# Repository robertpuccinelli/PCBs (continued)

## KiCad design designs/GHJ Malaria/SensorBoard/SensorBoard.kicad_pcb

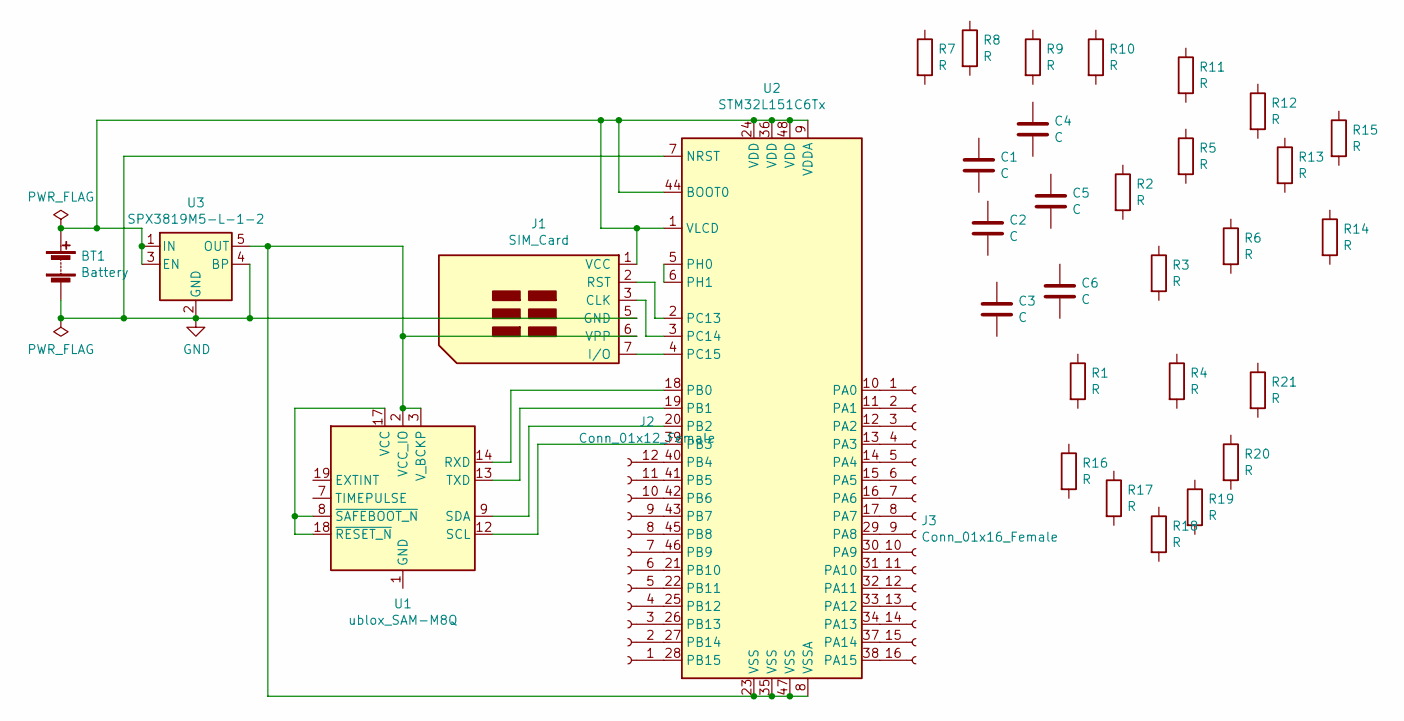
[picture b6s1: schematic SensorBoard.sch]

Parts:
BT1: Battery; BatteryHolder_Keystone_2468_2xAAA
C1, C2, C3, C4: C; C_1206_3216Metric
C5, C6: C; C_0603_1608Metric
J1: SIM_Card; USB_Mini-B_Lumberg_2486_01_Horizontal
J2: Conn_01x12_Female; PinSocket_1x12_P2.54mm_Vertical_SMD_Pin1Right
J3: Conn_01x16_Female; PinSocket_1x16_P2.54mm_Vertical_SMD_Pin1Right
R1, R2, R3, R7, R8, R9: R; R_01005_0402Metric
R4, R5, R6: R; R_0815_2038Metric
R10, R11, R12, R13, R14, R15, R16, R17, R18, R19, R20, R21: R; R_0603_1608Metric
U1: ublox_SAM-M8Q; SSOP-20_4.4x6.5mm_P0.65mm
U2: STM32L151C6Tx; LQFP-48_7x7mm_P0.5mm
U3: SPX3819M5-L-1-2; SOT-23-5

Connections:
GND: BT1.2 (-), J1.5 (GND), U2.7 (NRST), U3.2 (GND), U3.4 (BP)
unnamed: BT1.1 (+), J1.1 (VCC), U2.1 (VLCD), U2.9 (VDDA), U2.24 (VDD), U2.36 (VDD), U2.44 (BOOT0), U2.48 (VDD), U3.1 (IN), U3.3 (EN)
unnamed: J1.2 (RST), U2.2 (PC13)
unnamed: J1.3 (CLK), U2.3 (PC14)
unnamed: J1.6 (VPP), U1.2 (VCC_IO), U1.3 (V_BCKP), U2.8 (VSSA), U2.23 (VSS), U2.35 (VSS), U2.47 (VSS), U3.5 (OUT)
unnamed: J1.7 (I/O), U2.4 (PC15)
unnamed: J2.1, U2.28 (PB15)
unnamed: J2.2, U2.27 (PB14)
unnamed: J2.3, U2.26 (PB13)
unnamed: J2.4, U2.25 (PB12)
unnamed: J2.5, U2.22 (PB11)
unnamed: J2.6, U2.21 (PB10)
unnamed: J2.7, U2.46 (PB9)
unnamed: J2.8, U2.45 (PB8)
unnamed: J2.9, U2.43 (PB7)
unnamed: J2.10, U2.42 (PB6)
unnamed: J2.11, U2.41 (PB5)
unnamed: J2.12, U2.40 (PB4)
unnamed: J3.1, U2.10 (PA0)
unnamed: J3.2, U2.11 (PA1)
unnamed: J3.3, U2.12 (PA2)
unnamed: J3.4, U2.13 (PA3)
unnamed: J3.5, U2.14 (PA4)
unnamed: J3.6, U2.15 (PA5)
unnamed: J3.7, U2.16 (PA6)
unnamed: J3.8, U2.17 (PA7)
unnamed: J3.9, U2.29 (PA8)
unnamed: J3.10, U2.30 (PA9)
unnamed: J3.11, U2.31 (PA10)
unnamed: J3.12, U2.32 (PA11)
unnamed: J3.13, U2.33 (PA12)
unnamed: J3.14, U2.34 (PA13)
unnamed: J3.15, U2.37 (PA14)
unnamed: J3.16, U2.38 (PA15)
unnamed: U1.1 (GND), U1.4 (GND), U1.5 (GND), U1.6 (GND), U1.10 (GND), U1.11 (GND), U1.15 (GND), U1.16 (GND), U1.20 (GND)
unnamed: U1.9 (SDA), U2.20 (PB2)
unnamed: U1.12 (SCL), U2.39 (PB3)
unnamed: U1.13 (TXD), U2.19 (PB1)
unnamed: U1.14 (RXD), U2.18 (PB0)
unnamed: U1.8 (~SAFEBOOT_N), U1.17 (VCC), U1.18 (~RESET_N)
unnamed: U2.5 (PH0), U2.6 (PH1)

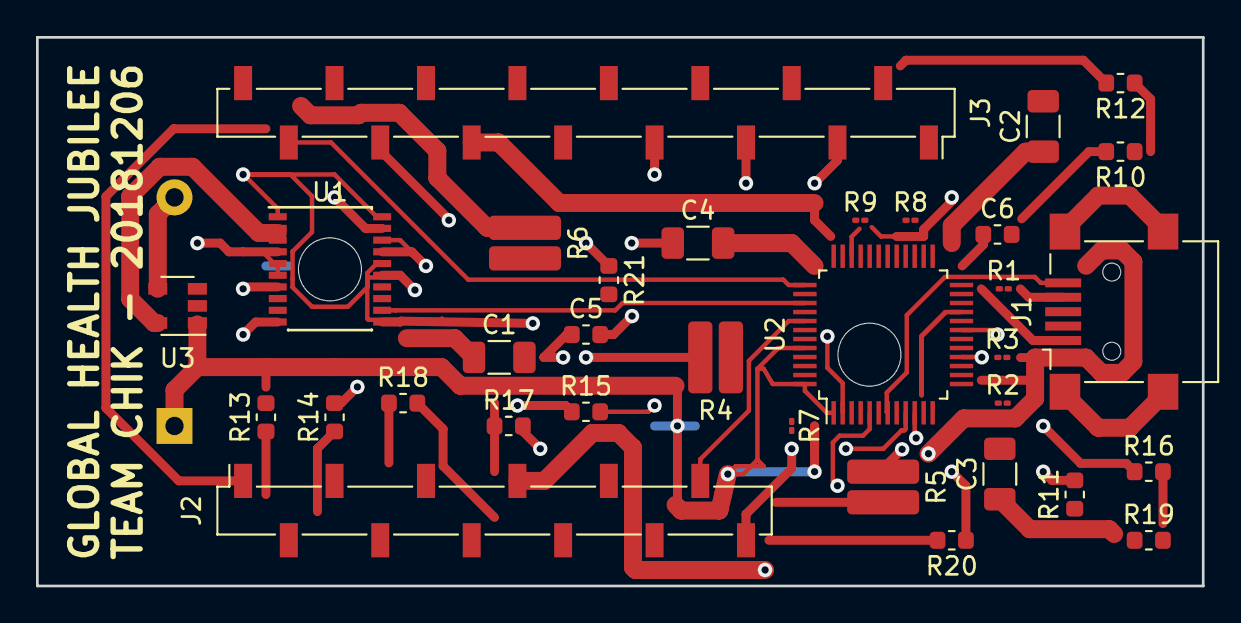
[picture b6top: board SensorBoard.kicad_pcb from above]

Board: 2 copper layers, 64.8 x 30.5 mm, 34 parts (1 on the bottom side), 40 nets.

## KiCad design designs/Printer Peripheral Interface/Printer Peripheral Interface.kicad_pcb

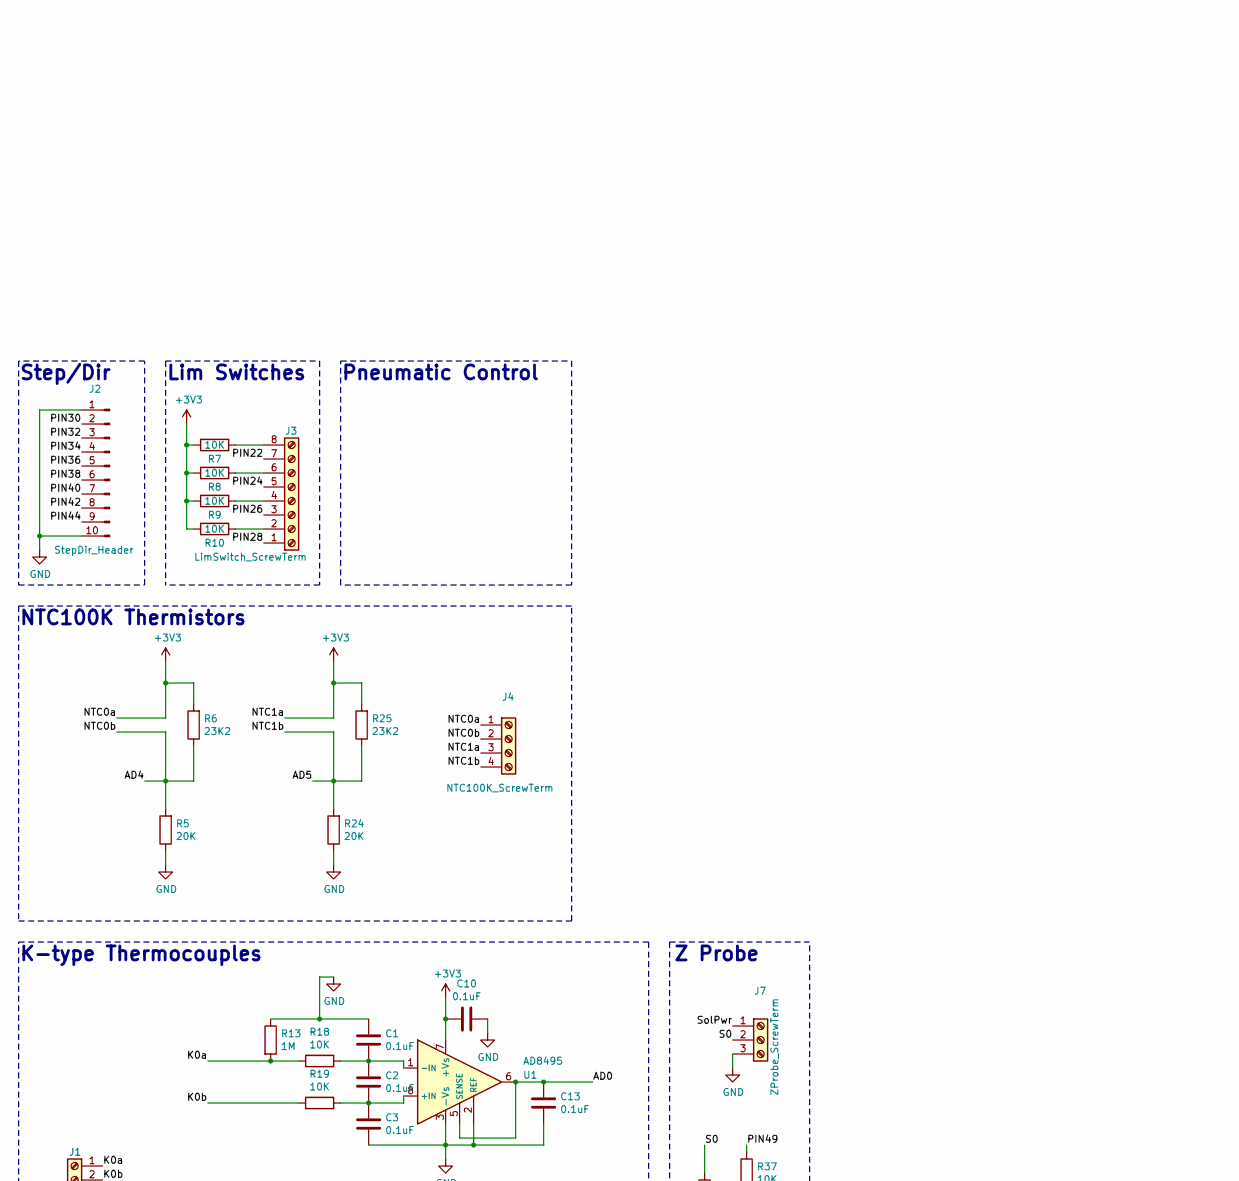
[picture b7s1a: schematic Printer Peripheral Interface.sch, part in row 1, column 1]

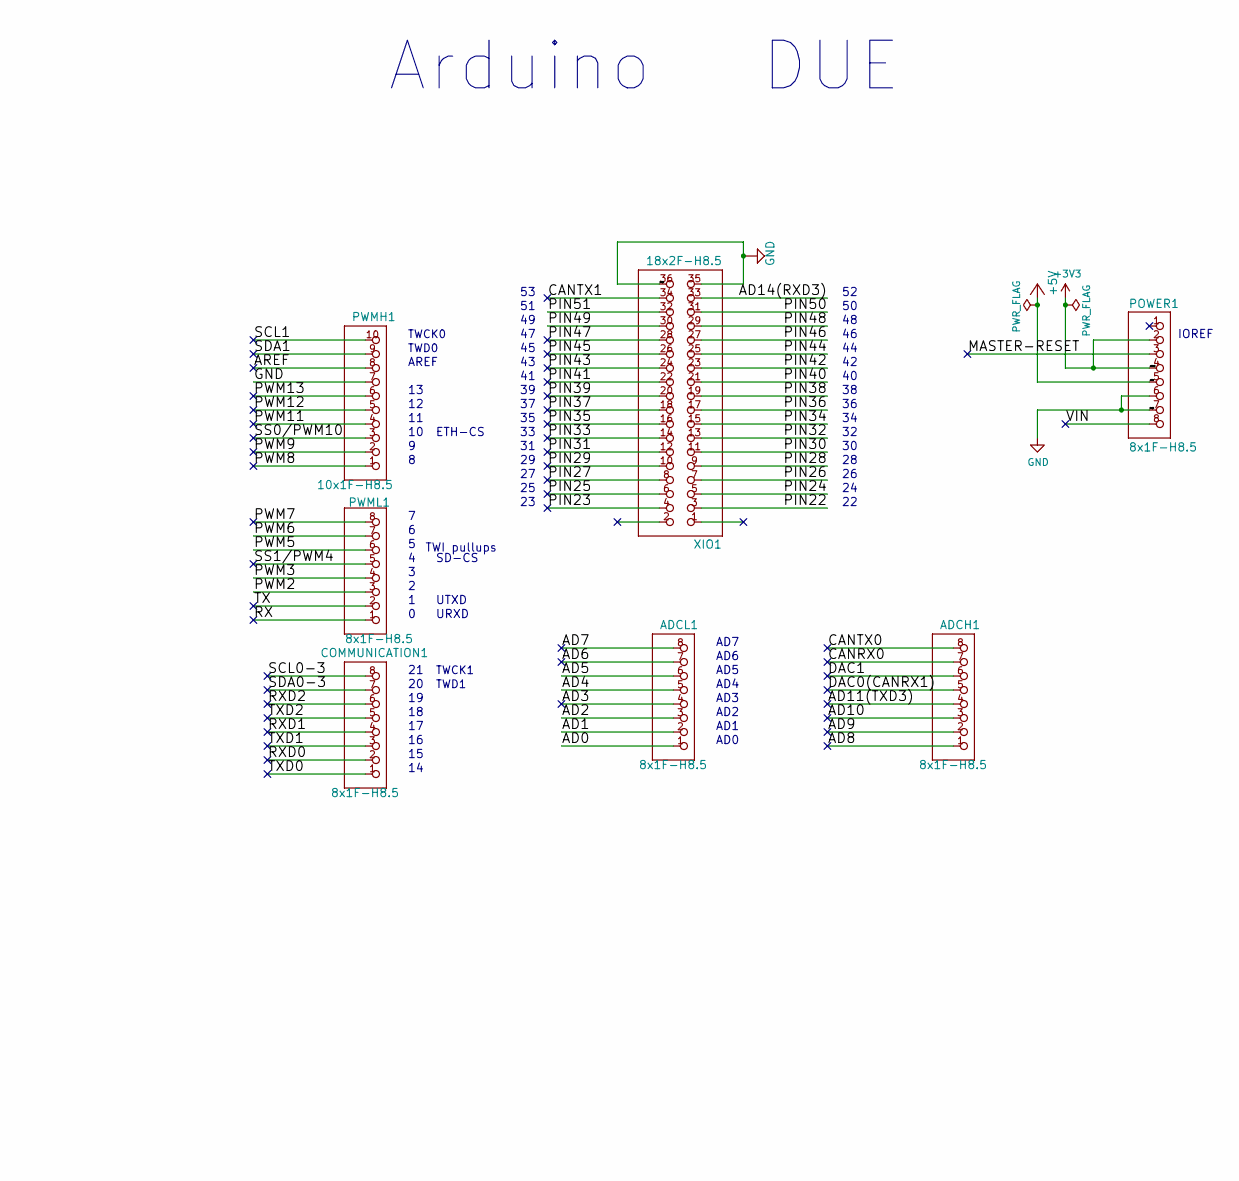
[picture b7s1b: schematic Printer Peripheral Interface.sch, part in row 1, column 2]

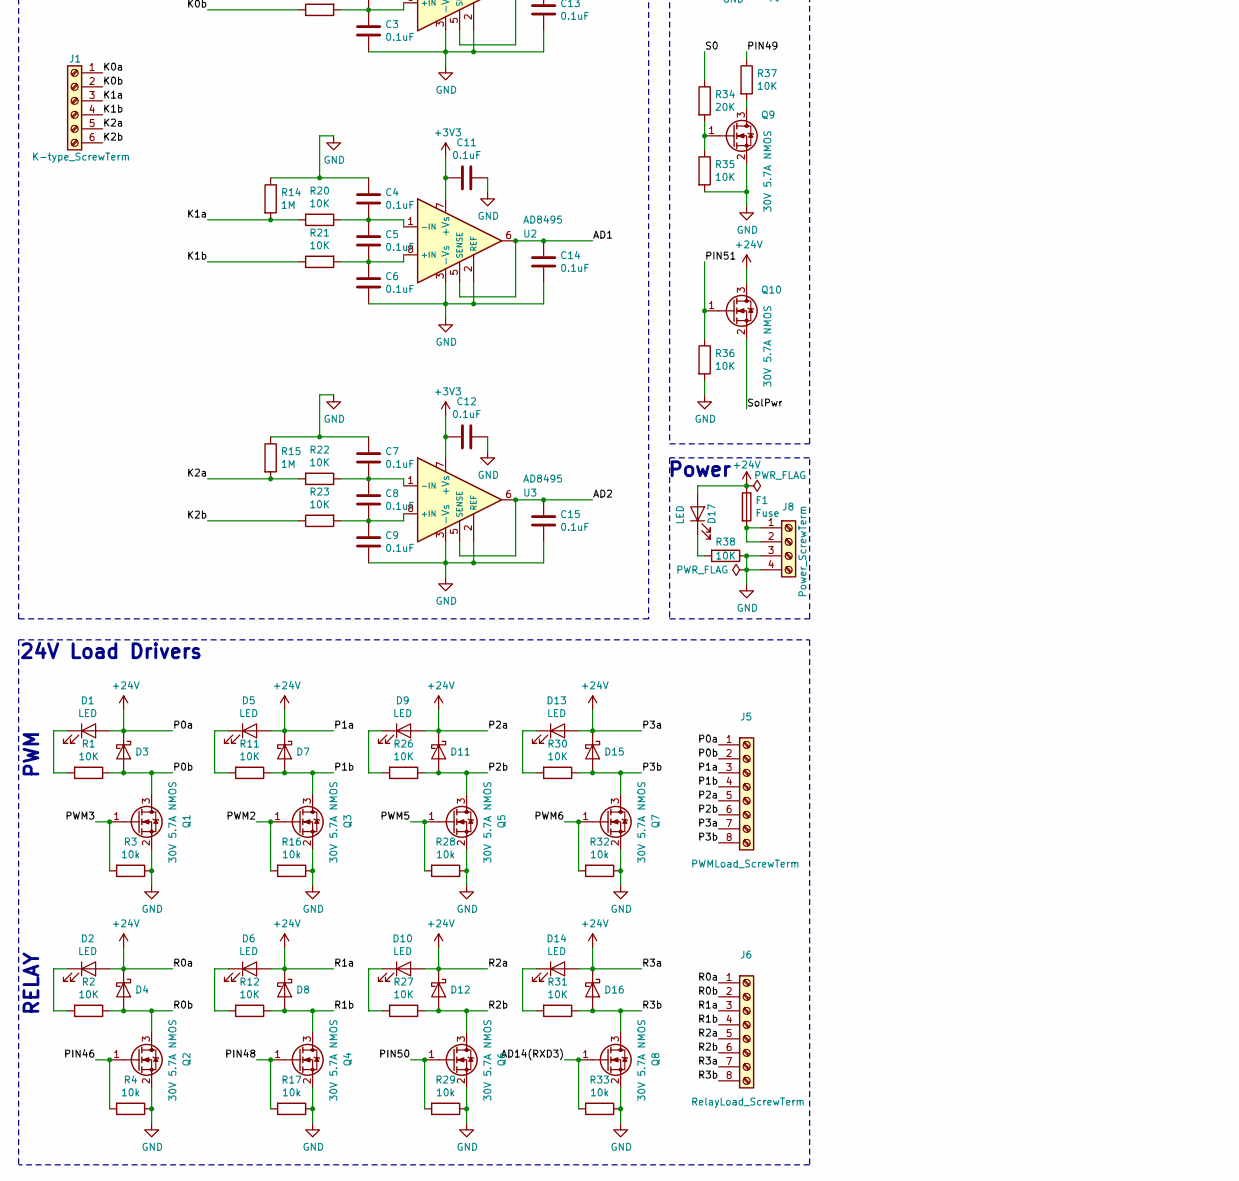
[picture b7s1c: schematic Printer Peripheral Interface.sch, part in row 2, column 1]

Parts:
ADCH1: 8x1F-H8.5; 1X08
ADCL1: 8x1F-H8.5; 1X08
C1, C2, C3, C4, C5, C6, C7, C8, C9, C10, C11, C12, C13, C14, C15: 0.1uF; C_0603_1608Metric
COMMUNICATION1: 8x1F-H8.5; 1X08
D1, D2, D5, D6, D9, D10, D13, D14, D17: LED; LED_0603_1608Metric
D3, D4, D7, D8, D11, D12, D15, D16: D_Schottky; D_SOD-123
F1: Fuse; Littelfuse_154Holder_Custom
J1: K-type_ScrewTerm; TerminalBlock_Phoenix_PT-1,5-6-3.5-H_1x06_P3.50mm_Horizontal
J2: StepDir_Header; PinHeader_1x10_P2.54mm_Vertical
J3: LimSwitch_ScrewTerm; TerminalBlock_Phoenix_PT-1,5-8-3.5-H_1x08_P3.50mm_Horizontal
J4: NTC100K_ScrewTerm; TerminalBlock_Phoenix_PT-1,5-4-3.5-H_1x04_P3.50mm_Horizontal
J5: PWMLoad_ScrewTerm; TerminalBlock_Phoenix_PT-1,5-8-3.5-H_1x08_P3.50mm_Horizontal
J6: RelayLoad_ScrewTerm; TerminalBlock_Phoenix_PT-1,5-8-3.5-H_1x08_P3.50mm_Horizontal
J7: ZProbe_ScrewTerm; TerminalBlock_Phoenix_PT-1,5-3-3.5-H_1x03_P3.50mm_Horizontal
J8: Power_ScrewTerm; TerminalBlock_Phoenix_PT-1,5-4-3.5-H_1x04_P3.50mm_Horizontal
POWER1: 8x1F-H8.5; 1X08
PWMH1: 10x1F-H8.5; 1X10
PWML1: 8x1F-H8.5; 1X08
Q1, Q2, Q3, Q4, Q5, Q6, Q7, Q8, Q9, Q10: 30V 5.7A NMOS; SOT-23
R1, R2, R7, R8, R9, R10, R11, R12, R18, R19, R20, R21, R22, R23, R26, R27, R30, R31, R35, R36, R37, R38: 10K; R_0603_1608Metric
R3, R4, R16, R17, R28, R29, R32, R33: 10k; R_0603_1608Metric
R5, R24, R34: 20K; R_0603_1608Metric
R6, R25: 23K2; R_0603_1608Metric
R13, R14, R15: 1M; R_0603_1608Metric
U1, U2, U3: AD8495; MSOP-8_3x3mm_P0.65mm
XIO1: 18x2F-H8.5; 2X18

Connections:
+3V3: C10.2, C11.2, C12.2, J4.1, J4.3, POWER1.2, POWER1.4, R6.2, R7.2, R8.2, R9.2, R10.2, R25.2, U1.7 (+Vs), U2.7 (+Vs), U3.7 (+Vs)
+5V: POWER1.5
+24V: D1.2 (A), D2.2 (A), D3.1 (K), D4.1 (K), D5.2 (A), D6.2 (A), D7.1 (K), D8.1 (K), D9.2 (A), D10.2 (A), D11.1 (K), D12.1 (K), D13.2 (A), D14.2 (A), D15.1 (K), D16.1 (K), D17.2 (A), F1.1, J5.1, J5.3, J5.5, J5.7, J6.1, J6.3, J6.5, J6.7, Q10.3 (D)
/AD0: ADCL1.1, C13.1, U1.5 (SENSE), U1.6
/AD1: ADCL1.2, C14.1, U2.5 (SENSE), U2.6
/AD2: ADCL1.3, C15.1, U3.5 (SENSE), U3.6
/AD3: ADCL1.4
/AD4: ADCL1.5, J4.2, R5.2, R6.1
/AD5: ADCL1.6, J4.4, R24.2, R25.1
/AD6: ADCL1.7
/AD7: ADCL1.8
/AD8: ADCH1.1
/AD9: ADCH1.2
/AD10: ADCH1.3
/AD11(TXD3): ADCH1.4
/AD14(RXD3): Q8.1 (G), R33.2, XIO1.33
/AREF: PWMH1.8
/CANRX0: ADCH1.7
/CANTX0: ADCH1.8
/CANTX1: XIO1.34
/DAC0(CANRX1): ADCH1.5
/DAC1: ADCH1.6
/K0a: J1.1, R13.2, R18.2
/K0b: J1.2, R19.1
/K1a: J1.3, R14.2, R20.2
/K1b: J1.4, R21.1
/K2a: J1.5, R15.2, R22.2
/K2b: J1.6, R23.1
/MASTER-RESET: POWER1.3
/P0b: D3.2 (A), J5.2, Q1.3 (D), R1.1
/P1b: D7.2 (A), J5.4, Q3.3 (D), R11.1
/P2b: D11.2 (A), J5.6, Q5.3 (D), R26.1
/P3b: D15.2 (A), J5.8, Q7.3 (D), R30.1
/PIN22: J3.7, XIO1.3
/PIN23: XIO1.4
/PIN24: J3.5, XIO1.5
/PIN25: XIO1.6
/PIN26: J3.3, XIO1.7
/PIN27: XIO1.8
/PIN28: J3.1, XIO1.9
/PIN29: XIO1.10
/PIN30: J2.2, XIO1.11
/PIN31: XIO1.12
/PIN32: J2.3, XIO1.13
/PIN33: XIO1.14
/PIN34: J2.4, XIO1.15
/PIN35: XIO1.16
/PIN36: J2.5, XIO1.17
/PIN37: XIO1.18
/PIN38: J2.6, XIO1.19
/PIN39: XIO1.20
/PIN40: J2.7, XIO1.21
/PIN41: XIO1.22
/PIN42: J2.8, XIO1.23
/PIN43: XIO1.24
/PIN44: J2.9, XIO1.25
/PIN45: XIO1.26
/PIN46: Q2.1 (G), R4.2, XIO1.27
/PIN47: XIO1.28
/PIN48: Q4.1 (G), R17.2, XIO1.29
/PIN49: R37.1, XIO1.30
/PIN50: Q6.1 (G), R29.2, XIO1.31
/PIN51: Q10.1 (G), R36.1, XIO1.32
/PWM2: PWML1.3, Q3.1 (G), R16.2
/PWM3: PWML1.4, Q1.1 (G), R3.2
/PWM5: PWML1.6, Q5.1 (G), R28.2
/PWM6: PWML1.7, Q7.1 (G), R32.2
/PWM7: PWML1.8
/PWM8: PWMH1.1
/PWM9: PWMH1.2
/PWM11: PWMH1.4
/PWM12: PWMH1.5
/PWM13: PWMH1.6
/R0b: D4.2 (A), J6.2, Q2.3 (D), R2.1
/R1b: D8.2 (A), J6.4, Q4.3 (D), R12.1
/R2b: D12.2 (A), J6.6, Q6.3 (D), R27.1
/R3b: D16.2 (A), J6.8, Q8.3 (D), R31.1
/RX: PWML1.1
/RXD0: COMMUNICATION1.2
/RXD1: COMMUNICATION1.4
/RXD2: COMMUNICATION1.6
/S0: J7.2, R34.1
/SCL0-3: COMMUNICATION1.8
/SCL1: PWMH1.10
/SDA0-3: COMMUNICATION1.7
/SDA1: PWMH1.9
/SS0/PWM10: PWMH1.3
/SS1/PWM4: PWML1.5
/SolPwr: J7.1, Q10.2 (S)
/TX: PWML1.2
/TXD0: COMMUNICATION1.1
/TXD1: COMMUNICATION1.3
/TXD2: COMMUNICATION1.5
/VIN: POWER1.8
GND: C1.1, C3.2, C4.1, C6.2, C7.1, C9.2, C10.1, C11.1, C12.1, C13.2, C14.2, C15.2, J2.1, J2.10, J7.3, J8.3, J8.4, POWER1.6, POWER1.7, PWMH1.7, Q1.2 (S), Q2.2 (S), Q3.2 (S), Q4.2 (S), Q5.2 (S), Q6.2 (S), Q7.2 (S), Q8.2 (S), Q9.2 (S), R3.1, R4.1, R5.1, R13.1, R14.1, R15.1, R16.1, R17.1, R24.1, R28.1, R29.1, R32.1, R33.1, R35.2, R36.2, R38.1, U1.2 (REF), U1.3 (-Vs), U2.2 (REF), U2.3 (-Vs), U3.2 (REF), U3.3 (-Vs), XIO1.35, XIO1.36
unnamed: C1.2, C2.1, R18.1, U1.1 (-IN)
unnamed: C2.2, C3.1, R19.2, U1.8 (+IN)
unnamed: C4.2, C5.1, R20.1, U2.1 (-IN)
unnamed: C5.2, C6.1, R21.2, U2.8 (+IN)
unnamed: C7.2, C8.1, R22.1, U3.1 (-IN)
unnamed: C8.2, C9.1, R23.2, U3.8 (+IN)
unnamed: D1.1 (K), R1.2
unnamed: D2.1 (K), R2.2
unnamed: D5.1 (K), R11.2
unnamed: D6.1 (K), R12.2
unnamed: D9.1 (K), R26.2
unnamed: D10.1 (K), R27.2
unnamed: D13.1 (K), R30.2
unnamed: D14.1 (K), R31.2
unnamed: D17.1 (K), R38.2
unnamed: F1.2, J8.1, J8.2
unnamed: J3.2, R10.1
unnamed: J3.4, R9.1
unnamed: J3.6, R8.1
unnamed: J3.8, R7.1
unnamed: Q9.1 (G), R34.2, R35.1
unnamed: Q9.3 (D), R37.2

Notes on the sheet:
TWI pullups
TWCK1
TWD1
IOREF
TWCK0
TWD0
AD1
AD2
AD3
AD4
AD5
AD6
AD0
AREF
AD7
SD-CS
UTXD
URXD
ETH-CS
Arduino DUE
K-type Thermocouples
NTC100K Thermistors
24V Load Drivers
Step/Dir
Lim Switches
PWM
RELAY
Pneumatic Control
Power
Z Probe

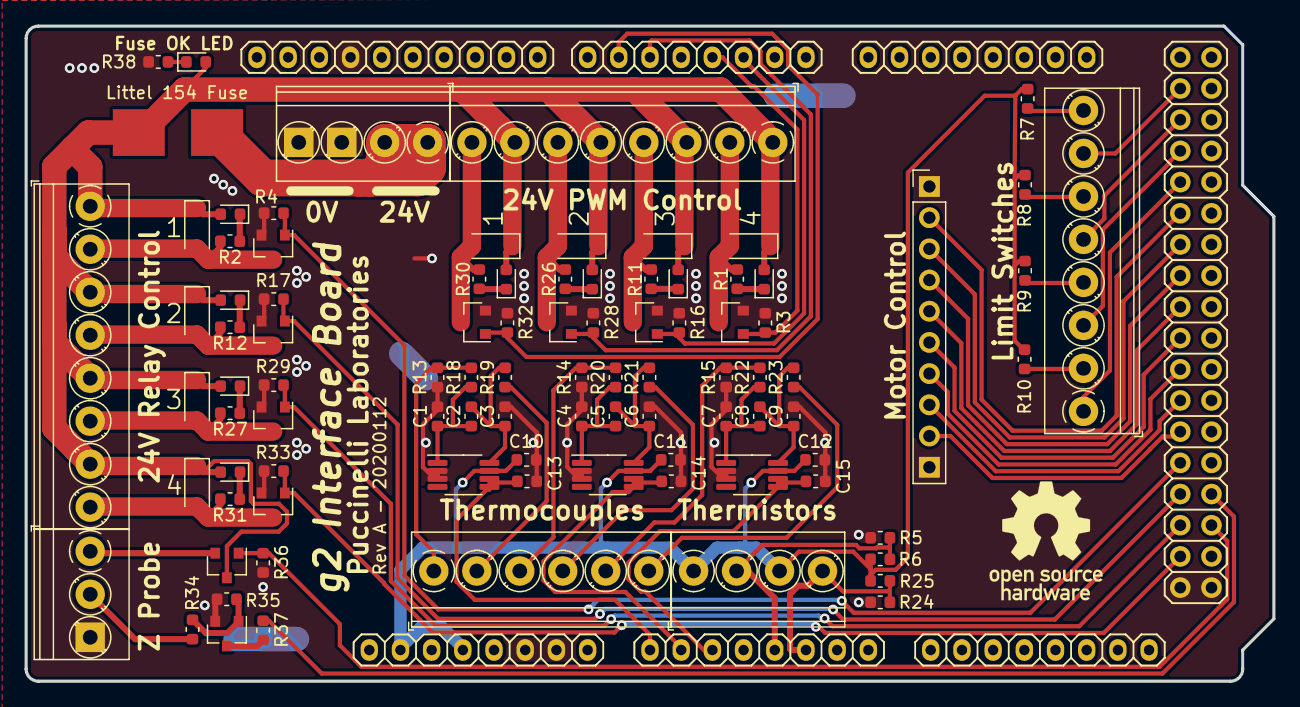
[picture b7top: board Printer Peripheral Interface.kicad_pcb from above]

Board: 2 copper layers, 101.6 x 53.3 mm, 99 parts (0 on the bottom side), 68 nets.

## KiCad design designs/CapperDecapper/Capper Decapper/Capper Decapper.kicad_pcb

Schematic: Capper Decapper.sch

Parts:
C1, C3, C7, C9, C13, C15, C22, C24: 22nF; C_0603_1608Metric
C2, C6, C8, C12, C14, C19, C23, C28, C29, C34, C35, C36, C37: 0.1uF; C_0603_1608Metric
C4, C10, C16, C25: 2.2uF; C_0603_1608Metric
C5, C11, C18, C27: 10nF; C_0603_1608Metric
C17, C20, C30, C31, C32, C33: 10uF; CP_EIA-3528-12_Kemet-T
C21: 0.33uF; C_0603_1608Metric
C26: 0.01uF; C_0603_1608Metric
D1, D2: Schottky; D_SMA
J1: Pi Control Signals; PinSocket_1x24_P2.54mm_Vertical
J2: Motor_Power; PinSocket_1x20_P2.54mm_Vertical
J3: Screw_Term; TerminalBlock_4Ucon_1x02_P3.50mm_Horizontal
L1: 22uH; L_Wuerth_HCI-1365
MH1, MH2: MountingHole; MountingHole_3mm
R1, R6, R7, R10, R12, R15, R16, R19: 0.05R; R_1206_3216Metric
R2, R5, R8, R9, R13, R14, R17, R18: 20k; R_0603_1608Metric
R3, R4: 330R; R_0603_1608Metric
R20: 14.2K; R_0603_1608Metric
R21: 2K; R_0603_1608Metric
U1, U4, U5, U8, U9, U12, U13, U18: INA214; SOT-363_SC-70-6
U2, U6, U10, U15: 74AHC08; PVQFN-14
U3, U7, U11, U16: DRV8833RTY; WQFN-16-1EP_4x4mm_P0.65mm_EP2.1x2.1mm
U14: L7805; TO-252-3_TabPin2
U17: MAX6018BEUR16; SOT-23
U19: AP1501A; TO-263-5_TabPin3

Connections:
/3.3V: J1.23, U17.1
/5V: C2.1, C6.1, C8.1, C12.1, C14.1, C19.1, C23.1, C28.1, C29.2, C34.1, C35.1, C36.1, C37.1, J1.22, U1.3 (V+), U2.14, U3.15, U4.3 (V+), U5.3 (V+), U6.14, U7.15, U8.3 (V+), U9.3 (V+), U10.14, U11.15, U12.3 (V+), U13.3 (V+), U14.3 (OUT), U15.14, U16.15, U18.3 (V+)
/ADC1: C3.1, J1.14, R5.1
/ADC2: C1.2, J1.15, R2.2
/ADC3: C9.1, J1.16, R9.1
/ADC4: C7.2, J1.17, R8.2
/ADC5: C15.1, J1.18, R14.1
/ADC6: C13.2, J1.19, R13.2
/ADC7: C24.1, J1.20, R18.1
/ADC8: C22.2, J1.21, R17.2
/EN1: J1.4, U2.10, U2.13
/EN2: J1.5, U2.2, U2.5
/EN3: J1.6, U6.10, U6.13
/EN4: J1.7, U6.2, U6.5
/EN5: J1.8, U10.10, U10.13
/EN6: J1.9, U10.2, U10.5
/EN7: J1.10, U15.10, U15.13
/EN8: J1.11, U15.2, U15.5
/FWD: J1.13, U2.1, U2.9, U6.1, U6.9, U10.1, U10.9, U15.1, U15.9
/MOT1_1: J2.4, R6.1, U4.4 (IN+)
/MOT1_2: J2.5, U3.2
/MOT2_1: J2.6, R1.2, U1.5 (IN-)
/MOT2_2: J2.7, U3.3
/MOT3_1: J2.8, R10.1, U8.4 (IN+)
/MOT3_2: J2.9, U7.2
/MOT4_1: J2.10, R7.2, U5.5 (IN-)
/MOT4_2: J2.11, U7.3
/MOT5_1: J2.12, R15.1, U12.4 (IN+)
/MOT5_2: J2.13, U11.2
/MOT6_1: J2.14, R12.2, U9.5 (IN-)
/MOT6_2: J2.15, U11.3
/MOT7_1: J2.16, R19.1, U18.4 (IN+)
/MOT7_2: J2.17, U16.2
/MOT8_1: J2.18, R16.2, U13.5 (IN-)
/MOT8_2: J2.19, U16.3
/REV: J1.12, U2.4, U2.12, U6.4, U6.12, U10.4, U10.12, U15.4, U15.12
/SOLSET: J1.3; also elsewhere on the board
/SW1: J2.2, R4.1
/SW2: J2.3, R3.2
/V_mon: C26.1, U1.1 (REF), U4.1 (REF), U5.1 (REF), U8.1 (REF), U9.1 (REF), U12.1 (REF), U13.1 (REF), U17.2, U18.1 (REF)
/V_motor: C5.2, C11.2, C17.1, C18.2, C20.1, C27.2, C30.1, C32.1, C33.1, L1.2, R20.2, U3.10, U7.10, U11.10, U16.10
GND: C1.1, C2.2, C3.2, C4.1, C6.2, C7.1, C8.2, C9.2, C10.1, C12.2, C13.1, C14.2, C15.2, C16.1, C17.2, C19.2, C20.2, C21.1, C22.1, C23.2, C24.2, C25.1, C26.2, C28.2, C29.1, C30.2, C31.2, C32.2, C33.2, C34.2, C35.2, C36.2, C37.2, D1.2, D2.2, J1.24, J2.20, J3.1, R21.2, U1.2 (GND), U2.7, U2.15, U3.1, U3.4, U3.11, U3.17, U4.2 (GND), U5.2 (GND), U6.7, U6.15, U7.1, U7.4, U7.11, U7.17, U8.2 (GND), U9.2 (GND), U10.7, U10.15, U11.1, U11.4, U11.11, U11.17, U12.2 (GND), U13.2 (GND), U14.2 (GND), U15.7, U15.15, U16.1, U16.4, U16.11, U16.17, U17.3, U18.2 (GND), U19.3, U19.5; also elsewhere on the board
unnamed: C4.2, U3.12
unnamed: C5.1, U3.9
unnamed: C10.2, U7.12
unnamed: C11.1, U7.9
unnamed: C16.2, U11.12
unnamed: C18.1, U11.9
unnamed: C25.2, U16.12
unnamed: C27.1, U16.9
unnamed: D2.1, L1.1, U19.2
unnamed: J1.1, R3.1
unnamed: J1.2, R4.2
unnamed: R1.1, U1.4 (IN+), U3.5
unnamed: R2.1, U1.6 (OUT)
unnamed: R5.2, U4.6 (OUT)
unnamed: R6.2, U3.16, U4.5 (IN-)
unnamed: R7.1, U5.4 (IN+), U7.5
unnamed: R8.1, U5.6 (OUT)
unnamed: R9.2, U8.6 (OUT)
unnamed: R10.2, U7.16, U8.5 (IN-)
unnamed: R12.1, U9.4 (IN+), U11.5
unnamed: R13.1, U9.6 (OUT)
unnamed: R14.2, U12.6 (OUT)
unnamed: R15.2, U11.16, U12.5 (IN-)
unnamed: R16.1, U13.4 (IN+), U16.5
unnamed: R17.1, U13.6 (OUT)
unnamed: R18.2, U18.6 (OUT)
unnamed: R19.2, U16.16, U18.5 (IN-)
unnamed: R20.1, R21.1, U19.4
unnamed: U2.3, U3.7
unnamed: U2.6, U3.8
unnamed: U2.8, U3.14
unnamed: U2.11, U3.13
unnamed: U6.3, U7.7
unnamed: U6.6, U7.8
unnamed: U6.8, U7.14
unnamed: U6.11, U7.13
unnamed: U10.3, U11.7
unnamed: U10.6, U11.8
unnamed: U10.8, U11.14
unnamed: U10.11, U11.13
unnamed: U15.3, U16.7
unnamed: U15.6, U16.8
unnamed: U15.8, U16.14
unnamed: U15.11, U16.13
VBUS: C21.2, C31.1, D1.1, J2.1, J3.2, U14.1 (IN), U19.1; also elsewhere on the board

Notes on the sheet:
Motor 9V
Solenoid Power
18V
V_monitor
Pi Control Signals
Motor Power
Half Bridges with Current Monitors

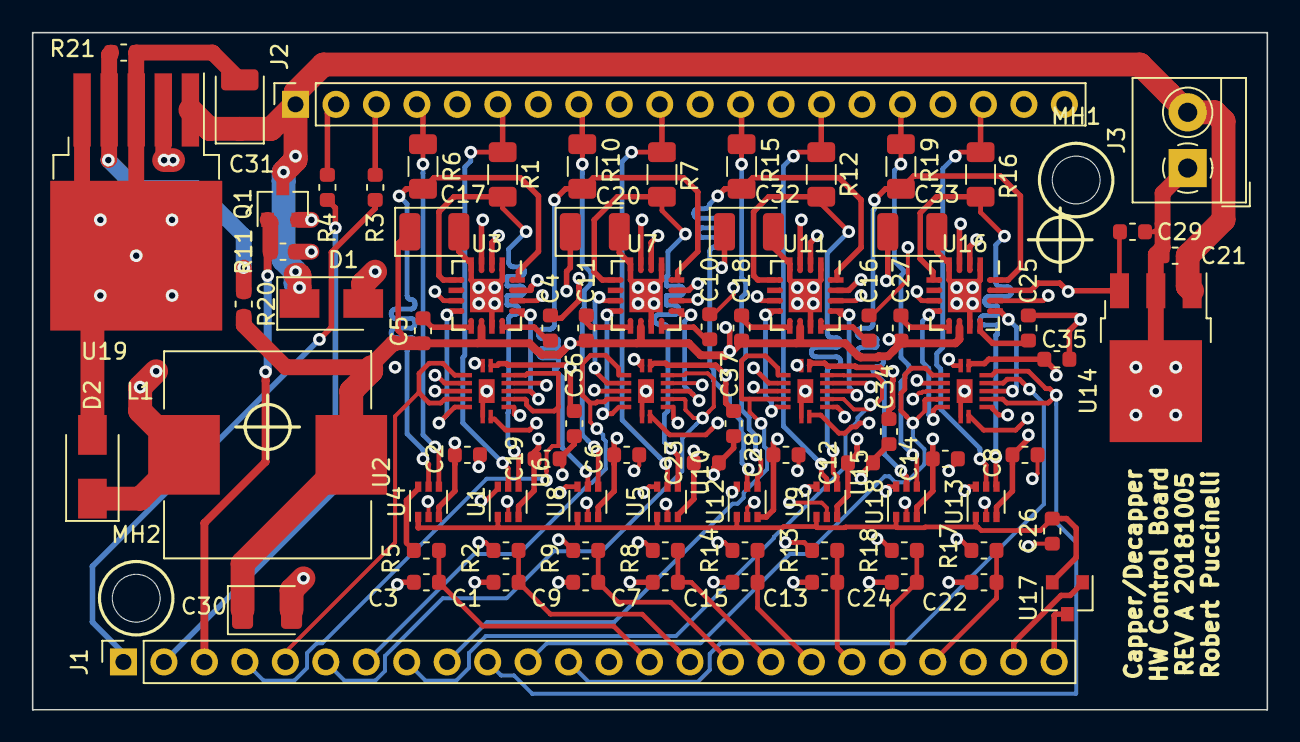
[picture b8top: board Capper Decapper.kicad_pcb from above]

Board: 4 copper layers, 77.5 x 42.5 mm, 86 parts (0 on the bottom side), 87 nets.

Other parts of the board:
Q1: Q_NMOS_GSD; SOT-23
R11: 5k; R_0603_1608Metric

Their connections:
/SOLSET: Q1.1, R11.2; also elsewhere on the board
GND: Q1.2, R11.1; also elsewhere on the board
VBUS: Q1.3; also elsewhere on the board

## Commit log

2018-04-16 initialized repo
2018-04-16 added submodules
2018-04-21 edited XC7Z035 and biofilms
2018-04-25 drafted v1 of biofilms PCB
2018-04-27 finalized v1 of biofilms PCB
2018-05-10 finalized v2 of biofilms PCB
2018-06-18 added in-situ prep pcb
2018-06-25 added capper decapper motor schematic
2018-09-05 Capper Decapper added with custom components
2018-09-08 converted to KiCAD 5
2018-09-10 complete 1st draft of capper/decapper PCB
2018-09-20 PWM capper decapper board
2018-10-05 Capper/Decapper HW Control Board Rev A
2018-10-09 AND gate updated, ordered
2018-12-13 Capper Decapper solenoid correction and solder dispensing files
2019-05-16 Directory update
2020-02-26 Update PCBs, Add autocapper board
2020-02-27 Capper Decapper REV B on OSHPark
2020-02-28 Update schematic
2020-03-04 Add printer, global IoT, and Nucelo test boards
2020-03-04 Add capper v2 corrections
2020-03-10 Update R1 design files
2020-05-18 Add P1 Rev A, update R1 files, add initial M1, add gerber2graphtec
2020-05-21 P1 Programmer Rev A
2020-05-21 Update LEDs on P1 3D model
2020-05-21 Initial D1, R1 Rev B
2020-05-22 Corrected doubled symbol issue on R1
2020-05-24 Update P1 Rev B, R1 Rev B, D1 Rev A
2020-05-24 R4R: P1 Rev B, R1 Rev B
2020-05-27 R4R D1 Rev A
2020-05-30 Ordered: D1 Rev A, R1 Rev B, P1 Rev B
2020-06-06 M1 Rev A, minor component changes in schematic
2020-07-28 Move Vespucci and add adc array
2020-09-28 Add initial DLS design
2020-10-03 Update schematic and board layout, Rev A
2020-10-03 Update schematic PDF
2020-10-11 Add initial Pi 3B bare metal code
2020-10-11 Removed custom buffer files
2020-10-25 Add host python interface
2020-10-25 Add cross compiled RPi files, update Python interface
2023-07-14 move pcb designs to seperate repos
2023-07-14 remove legacy libraries
2023-07-21 Add official repo as submodule, add new parts for PLOD1
2024-07-17 Add microfluidics footprints to custom library
2025-02-04 Add microfluidic features
2025-02-06 Add components for microfluidic hardware
2025-02-06 Add microfluidic hardware components
